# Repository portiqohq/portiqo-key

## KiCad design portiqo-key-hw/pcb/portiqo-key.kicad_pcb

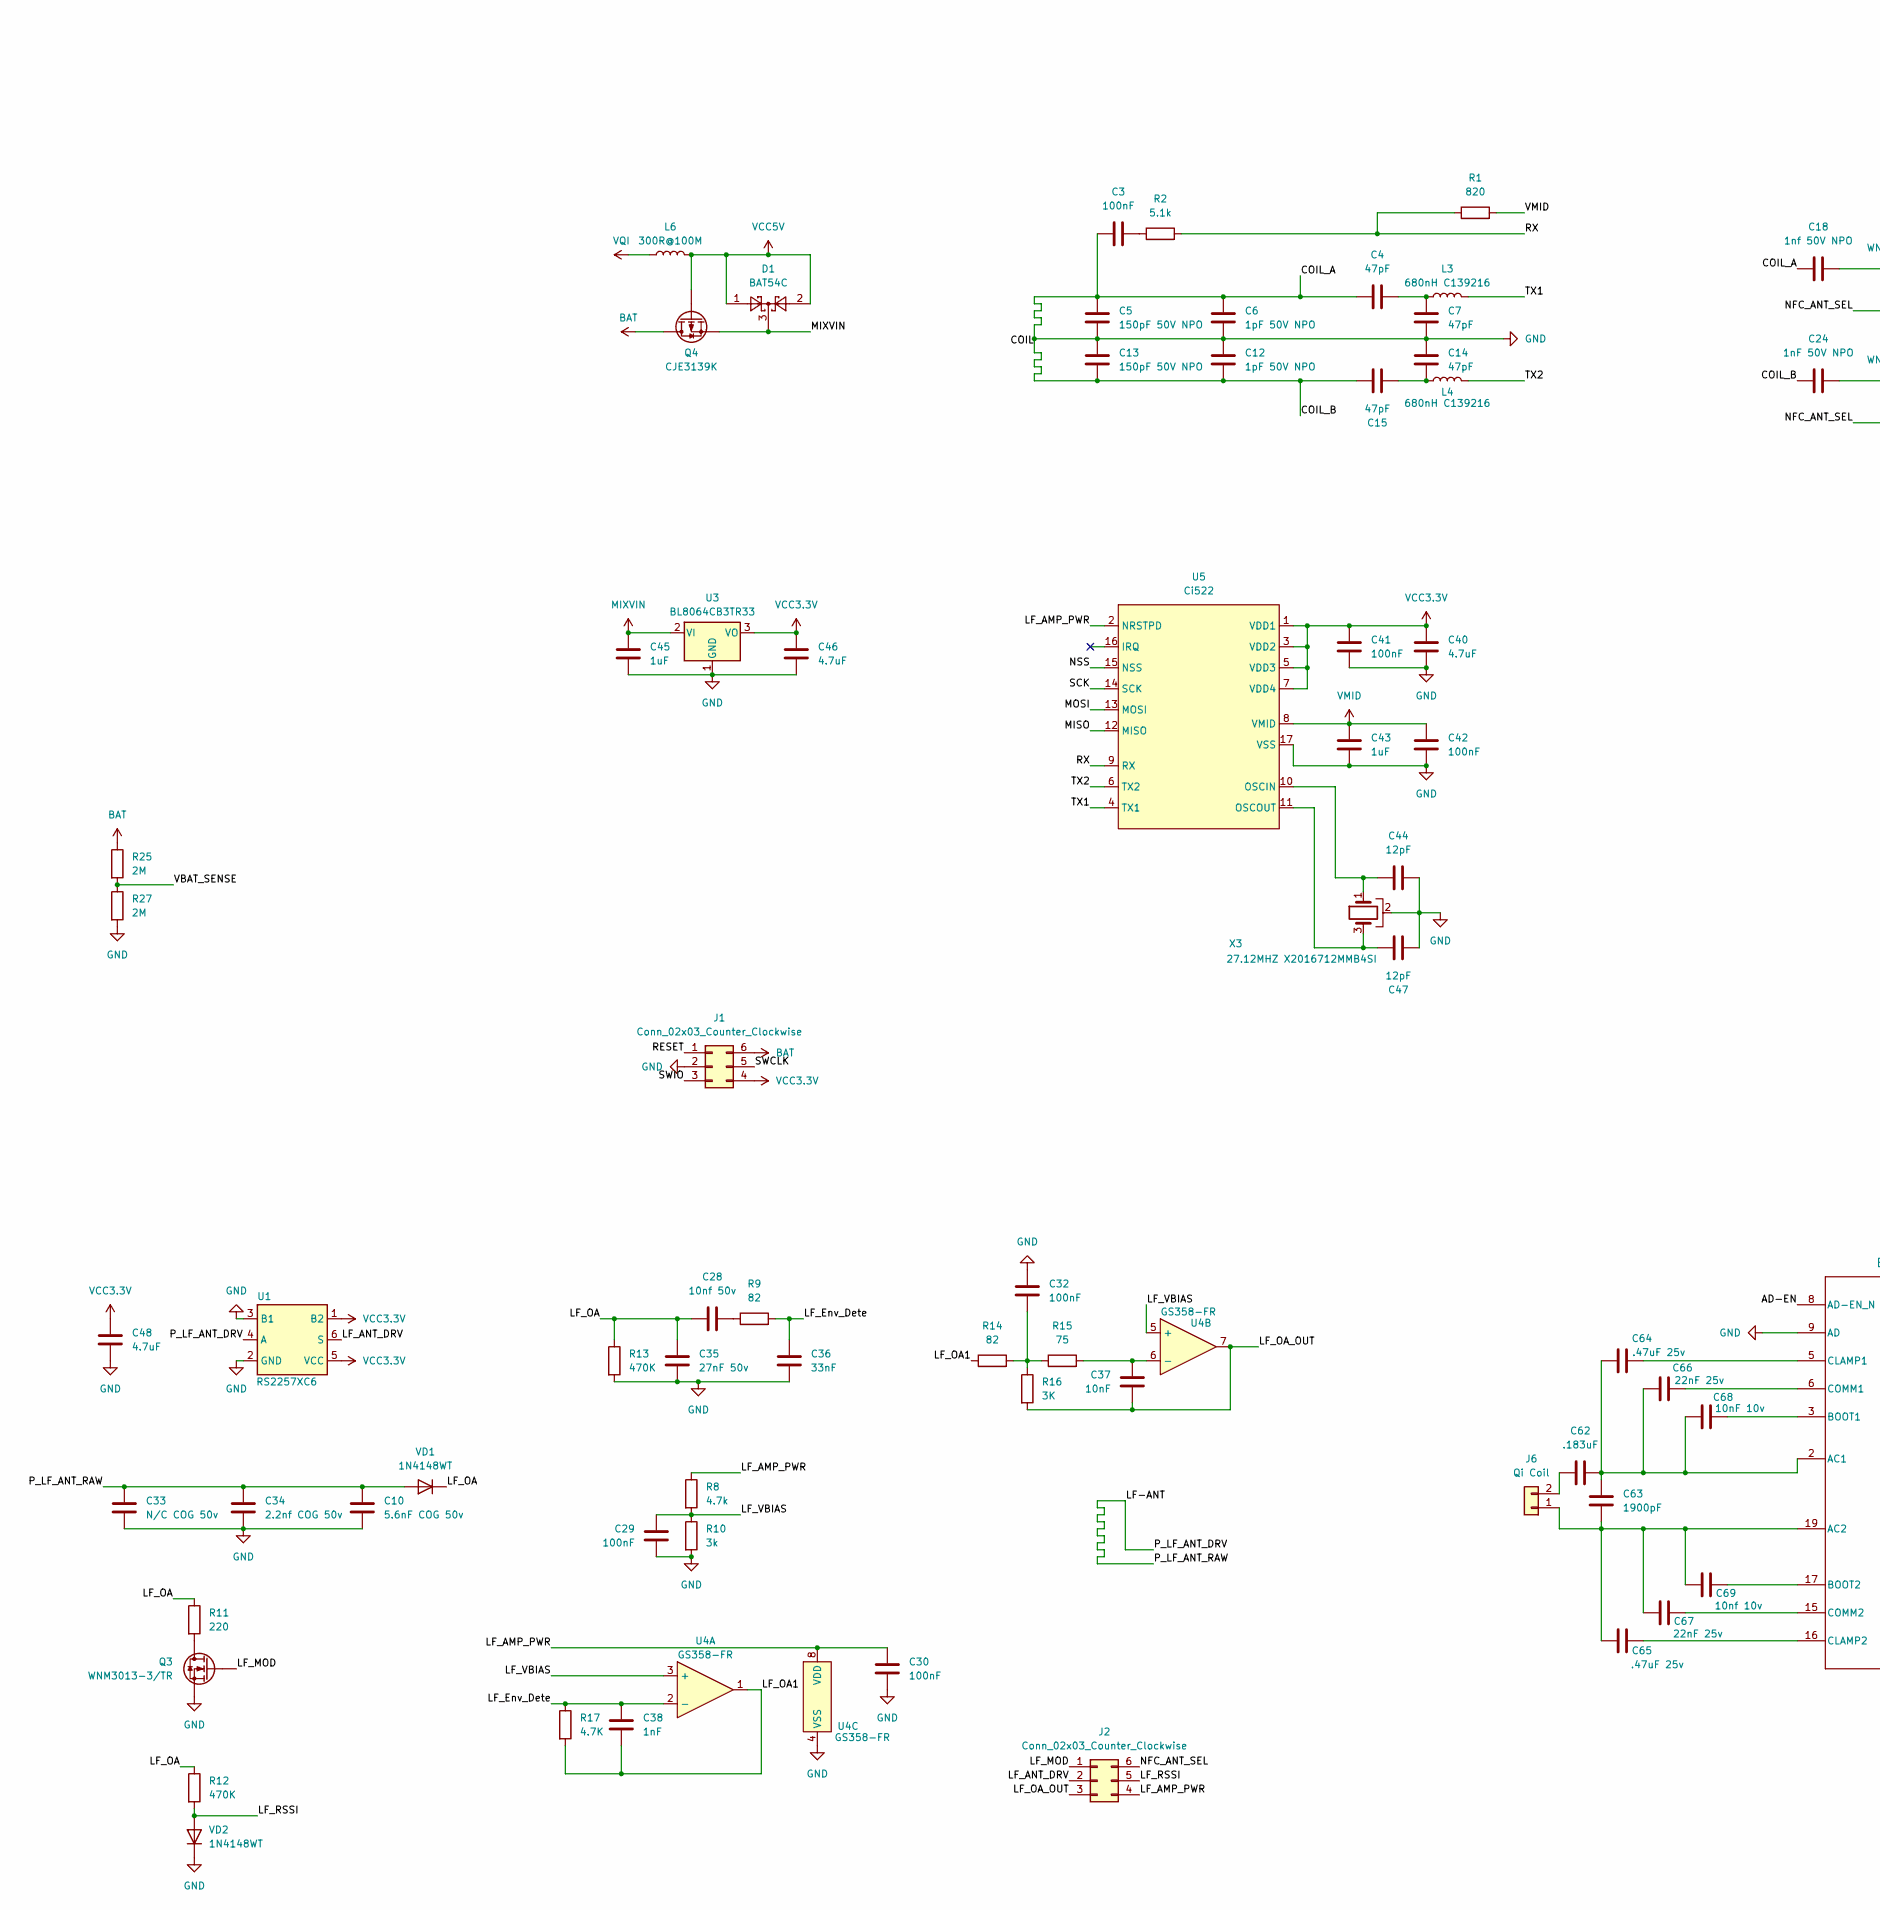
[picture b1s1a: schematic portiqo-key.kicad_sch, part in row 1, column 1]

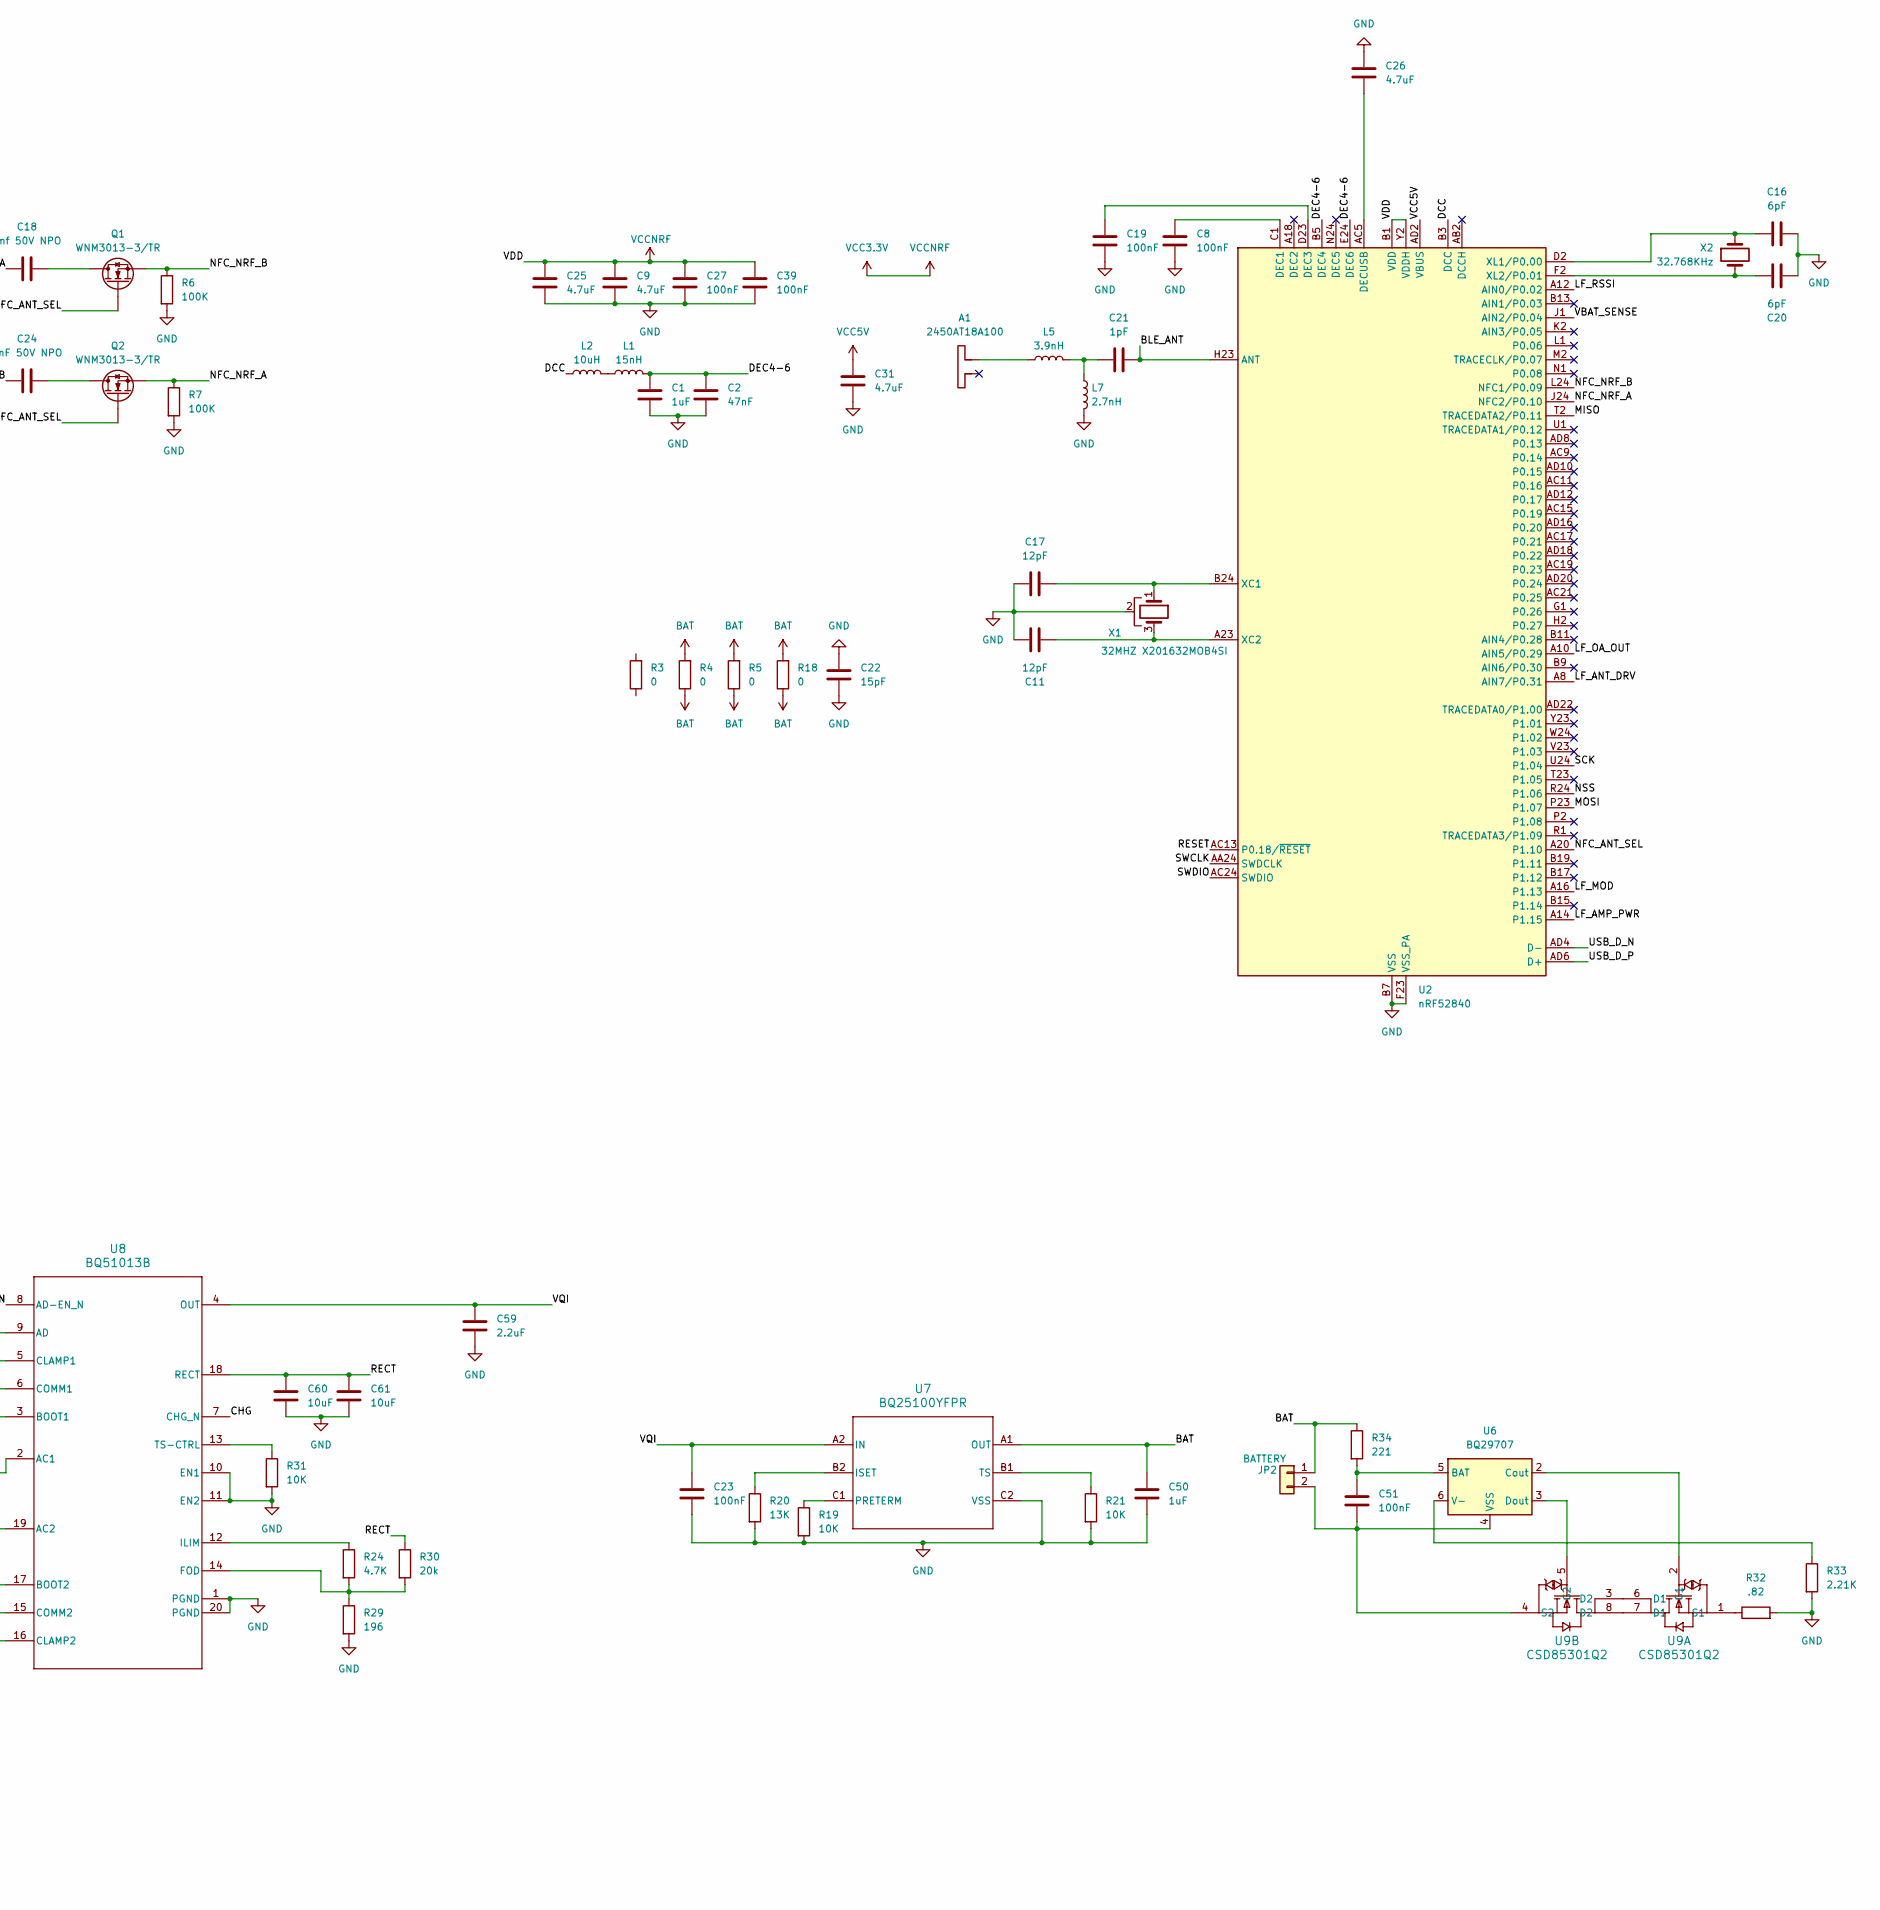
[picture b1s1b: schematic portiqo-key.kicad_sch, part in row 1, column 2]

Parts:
A1: 2450AT18A100; Johanson_2450AT18x100
C1, C43, C45, C50: 1uF; C_0402_1005Metric
C2: 47nF; C_0402_1005Metric
C3, C8, C19, C23, C27, C29, C30, C32, C39, C41, C42, C51: 100nF; C_0402_1005Metric
C4, C7, C14, C15: 47pF; C_0402_1005Metric
C5, C13: 150pF 50V NPO; C_0402_1005Metric
C6, C12: 1pF 50V NPO; C_0402_1005Metric
C9, C25, C26, C31, C40, C46, C48: 4.7uF; C_0402_1005Metric
C10: 5.6nF COG 50v; C_0402_1005Metric
C11, C17, C44, C47: 12pF; C_0402_1005Metric
C16, C20: 6pF; C_0402_1005Metric
C18: 1nf 50V NPO; C_0402_1005Metric
C21: 1pF; C_0402_1005Metric
C22: 15pF; C_0402_1005Metric
C24: 1nF 50V NPO; C_0402_1005Metric
C28: 10nf 50v; C_0402_1005Metric
C33: N/C COG 50v; C_0402_1005Metric
C34: 2.2nf COG 50v; C_0402_1005Metric
C35: 27nF 50v; C_0402_1005Metric
C36: 33nF; C_0402_1005Metric
C37: 10nF; C_0402_1005Metric
C38: 1nF; C_0402_1005Metric
C59: 2.2uF; C_0402_1005Metric
C60, C61: 10uF; C_0402_1005Metric
C62: .183uF; C_0402_1005Metric
C63: 1900pF; C_0402_1005Metric
C64, C65: .47uF 25v; C_0402_1005Metric
C66, C67: 22nF 25v; C_0402_1005Metric
C68: 10nF 10v; C_0402_1005Metric
C69: 10nf 10v; C_0402_1005Metric
D1: BAT54C; SOT-23
J1, J2: Conn_02x03_Counter_Clockwise; Tag-Connect_TC2030-IDC-NL_2x03_P1.27mm_Vertical
J6: Qi Coil; Solderpad - 2 pin
JP2: BATTERY; Solderpad - 2 pin
L1: 15nH; L_0402_1005Metric
L2: 10uH; L_0603_1608Metric
L3, L4: 680nH C139216; L_0603_1608Metric
L5: 3.9nH; L_0402_1005Metric
L6: 300R@100M; L_0402_1005Metric
L7: 2.7nH; L_0402_1005Metric
Q1, Q2, Q3: WNM3013-3/TR; SOT-723
Q4: CJE3139K; SOT-523
R1: 820; R_0402_1005Metric
R2: 5.1k; R_0402_1005Metric
R3, R4, R5, R18: 0; R_0402_1005Metric
R6, R7: 100K; R_0402_1005Metric
R8: 4.7k; R_0402_1005Metric
R9, R14: 82; R_0402_1005Metric
R10: 3k; R_0402_1005Metric
R11: 220; R_0402_1005Metric
R12, R13: 470K; R_0402_1005Metric
R15: 75; R_0402_1005Metric
R16: 3K; R_0402_1005Metric
R17, R24: 4.7K; R_0402_1005Metric
R19, R21, R31: 10K; R_0402_1005Metric
R20: 13K; R_0402_1005Metric
R25, R27: 2M; R_0402_1005Metric
R29: 196; R_0402_1005Metric
R30: 20k; R_0402_1005Metric
R32: .82; R_0402_1005Metric
R33: 2.21K; R_0402_1005Metric
R34: 221; R_0402_1005Metric
U1: RS2257XC6; SOT-363_SC-70-6
U2: nRF52840; Nordic_AQFN-73-1EP_7x7mm_P0.5mm
U3: BL8064CB3TR33; SOT-23
U4: GS358-FR; DFN-8-1EP_2x2mm_P0.5mm_EP0.9x1.3mm
U5: Ci522; QFN-16-1EP_3x3mm_P0.5mm_EP1.9x1.9mm
U6: BQ29707; WSON-6_1.5x1.5mm_P0.5mm
U7: BQ25100YFPR; YFP0006AFAV
U8: BQ51013B; RHL20_2P05X3P05
U9: CSD85301Q2; DQK0006B
VD1, VD2: 1N4148WT; D_SOD-523
X1: 32MHZ X201632MOB4SI; Crystal_SMD_2016-4Pin_2.0x1.6mm
X2: 32.768KHz; SMD1610-2P X161032768KGD2SI CRYSTAL
X3: 27.12MHZ X2016712MMB4SI; Crystal_SMD_2016-4Pin_2.0x1.6mm

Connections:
/AD-EN: U8.8 (AD-EN_N)
/BLE_ANT: C21.2, U2.H23 (ANT)
/CHG: U8.7 (CHG_N)
/DCC: L2.1, U2.B3 (DCC)
/DEC4-6: C1.1, C2.1, L1.2, U2.B5 (DEC4), U2.E24 (DEC6)
/LF-ANT: C10.1, C33.1, C34.1, U1.4 (A), VD1.2 (A)
/LF_AMP_PWR: C30.1, J2.4, R8.1, U2.A14 (P1.15), U4.8 (VDD), U5.2 (NRSTPD)
/LF_ANT_DRV: J2.2, U1.6 (S), U2.A8 (AIN7/P0.31)
/LF_Env_Dete: C36.1, C38.1, R9.2, R17.1, U4.2 (-)
/LF_MOD: J2.1, Q3.G, U2.A16 (P1.13)
/LF_OA: C28.2, C35.1, R11.1, R12.1, R13.1, VD1.1 (K)
/LF_OA1: C38.2, R14.1, R17.2, U4.1
/LF_OA_OUT: C37.2, J2.3, R16.2, U2.A10 (AIN5/P0.29), U4.7
/LF_RSSI: J2.5, R12.2, U2.A12 (AIN0/P0.02), VD2.2 (A)
/LF_VBIAS: C29.1, R8.2, R10.1, U4.3 (+), U4.5 (+)
/MISO: U2.T2 (TRACEDATA2/P0.11), U5.12 (MISO)
/MOSI: U2.P23 (P1.07), U5.13 (MOSI)
/NFC_ANT_SEL: J2.6, Q1.G, Q2.G, U2.A20 (P1.10)
/NFC_NRF_A: Q2.S, R7.1, U2.J24 (NFC2/P0.10)
/NFC_NRF_B: Q1.S, R6.1, U2.L24 (NFC1/P0.09)
/NSS: U2.R24 (P1.06), U5.15 (NSS)
/RECT: C60.1, C61.1, R30.1, U8.18 (RECT)
/RESET: J1.1, U2.AC13 (P0.18/~RESET)
/RX: R1.1, R2.2, U5.9 (RX)
/SCK: U2.U24 (P1.04), U5.14 (SCK)
/SWCLK: J1.5, U2.AA24 (SWDCLK)
/TX1: L3.2, U5.4 (TX1)
/TX2: L4.1, U5.6 (TX2)
/USB_D_N: U2.AD4 (D-)
/USB_D_P: U2.AD6 (D+)
/VBAT_SENSE: R25.2, R27.1, U2.J1 (AIN2/P0.04)
BAT: C50.1, J1.6, JP2.1, Q4.D, R4.1, R4.2, R5.1, R5.2, R18.1, R18.2, R25.1, R34.1, U7.A1 (OUT)
GND: C1.2, C2.2, C3.1, C4.1, C5.1, C5.2, C6.1, C6.2, C7.2, C8.2, C9.2, C10.2, C11.1, C12.1, C12.2, C13.1, C13.2, C14.1, C15.2, C16.2, C17.1, C18.2, C19.2, C20.2, C22.1, C22.2, C23.2, C24.2, C25.2, C26.1, C27.2, C29.2, C30.2, C31.2, C32.1, C33.2, C34.2, C35.2, C36.2, C39.2, C40.2, C41.2, C42.2, C43.2, C44.2, C45.2, C46.2, C47.2, C48.2, C50.2, C59.2, C60.2, C61.2, J1.2, L7.2, Q3.S, R6.2, R7.2, R10.2, R13.2, R19.2, R20.2, R21.2, R27.2, R29.2, R31.2, R32.2, R33.2, U1.2 (GND), U1.3 (B1), U2.B7 (VSS), U2.EP (VSS), U2.F23 (VSS_PA), U3.1 (GND), U4.4 (VSS), U5.17 (VSS), U7.C2 (VSS), U8.1 (PGND), U8.9 (AD), U8.10 (EN1), U8.11 (EN2), U8.20 (PGND), U8.21, VD2.1 (K), X1.2, X3.2
MIXVIN: C45.1, D1.3, Q4.S, U3.2 (VI)
unnamed: A1.2, L5.1
unnamed: C3.2, R2.1
unnamed: C4.2, C7.1, L3.1
unnamed: C14.2, C15.1, L4.2
unnamed: C18.1, Q1.D
unnamed: C21.1, L5.2, L7.1
unnamed: C24.1, Q2.D
unnamed: C28.1, R9.1
unnamed: C32.2, R14.2, R15.1, R16.1
unnamed: C63.2, C65.1, C67.1, C69.1, J6.1, U8.19 (AC2)
unnamed: C62.1, J6.2
unnamed: C51.2, JP2.2, U6.4 (VSS), U9.4 (S2)
unnamed: L1.1, L2.2
unnamed: Q3.D, R11.2
unnamed: C8.1, U2.C1 (DEC1)
unnamed: C19.1, U2.D23 (DEC3)
unnamed: C26.2, U2.AC5 (DECUSB)
unnamed: C17.2, U2.B24 (XC1), X1.1
unnamed: C11.2, U2.A23 (XC2), X1.3
unnamed: C16.1, U2.D2 (XL1/P0.00), X2.1
unnamed: C20.1, U2.F2 (XL2/P0.01), X2.2
unnamed: C37.1, R15.2, U4.6 (-)
unnamed: C44.1, U5.10 (OSCIN), X3.1
unnamed: C47.1, U5.11 (OSCOUT), X3.3
unnamed: C51.1, R34.2, U6.5 (BAT)
unnamed: U6.2 (Cout), U9.2 (G1)
unnamed: U6.3 (Dout), U9.5 (G2)
unnamed: R33.1, U6.6 (V-)
unnamed: R20.1, U7.B2 (ISET)
unnamed: R19.1, U7.C1 (PRETERM)
unnamed: R21.1, U7.B1 (TS)
unnamed: C62.2, C63.1, C64.1, C66.1, C68.1, U8.2 (AC1)
unnamed: C68.2, U8.3 (BOOT1)
unnamed: C69.2, U8.17 (BOOT2)
unnamed: C64.2, U8.5 (CLAMP1)
unnamed: C65.2, U8.16 (CLAMP2)
unnamed: C66.2, U8.6 (COMM1)
unnamed: C67.2, U8.15 (COMM2)
unnamed: R24.2, R29.1, R30.2, U8.14 (FOD)
unnamed: R24.1, U8.12 (ILIM)
unnamed: R31.1, U8.13 (TS-CTRL)
unnamed: U9.3 (D2), U9.6 (D1)
unnamed: U9.7 (D1), U9.8 (D2)
unnamed: R32.1, U9.1 (S1)
VCC3.3V: C9.1, C25.1, C27.1, C39.1, C40.1, C41.1, C46.1, C48.1, J1.4, U1.1 (B2), U1.5 (VCC), U2.A22 (VDD), U2.AD14 (VDD), U2.AD23 (VDD), U2.B1 (VDD), U2.W1 (VDD), U2.Y2 (VDDH), U3.3 (VO), U5.1 (VDD1), U5.3 (VDD2), U5.5 (VDD3), U5.7 (VDD4)
VCC5V: C31.1, D1.1, D1.2, L6.2, Q4.G, U2.AD2 (VBUS)
VMID: C42.1, C43.1, R1.2, U5.8 (VMID)
VQI: C23.1, C59.1, L6.1, U7.A2 (IN), U8.4 (OUT)

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
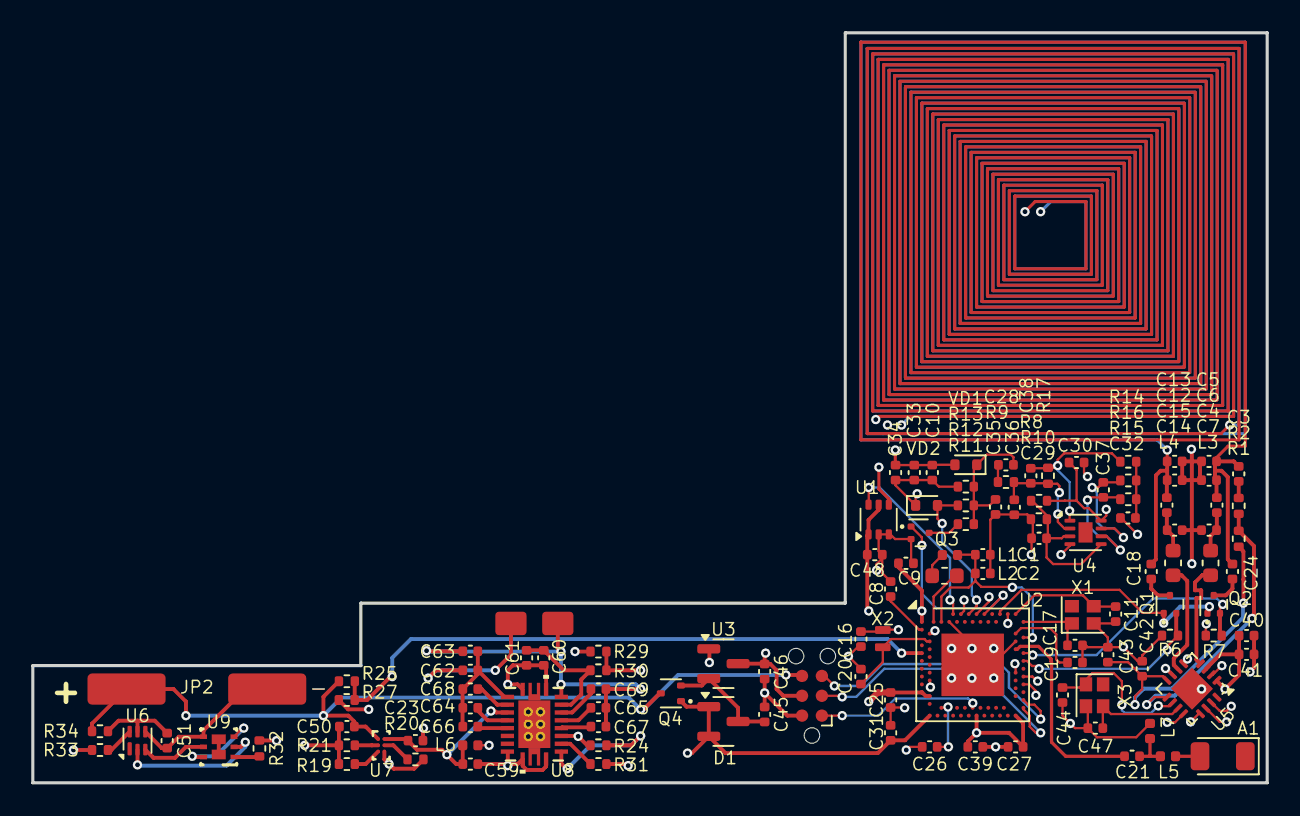
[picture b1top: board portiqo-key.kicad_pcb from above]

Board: 4 copper layers, 79.0 x 48.0 mm, 116 parts (0 on the bottom side), 79 nets.

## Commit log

2025-07-18 Updated schematic for wireless charging. Added footprints for most ICs
2025-07-25 HW V0.1
